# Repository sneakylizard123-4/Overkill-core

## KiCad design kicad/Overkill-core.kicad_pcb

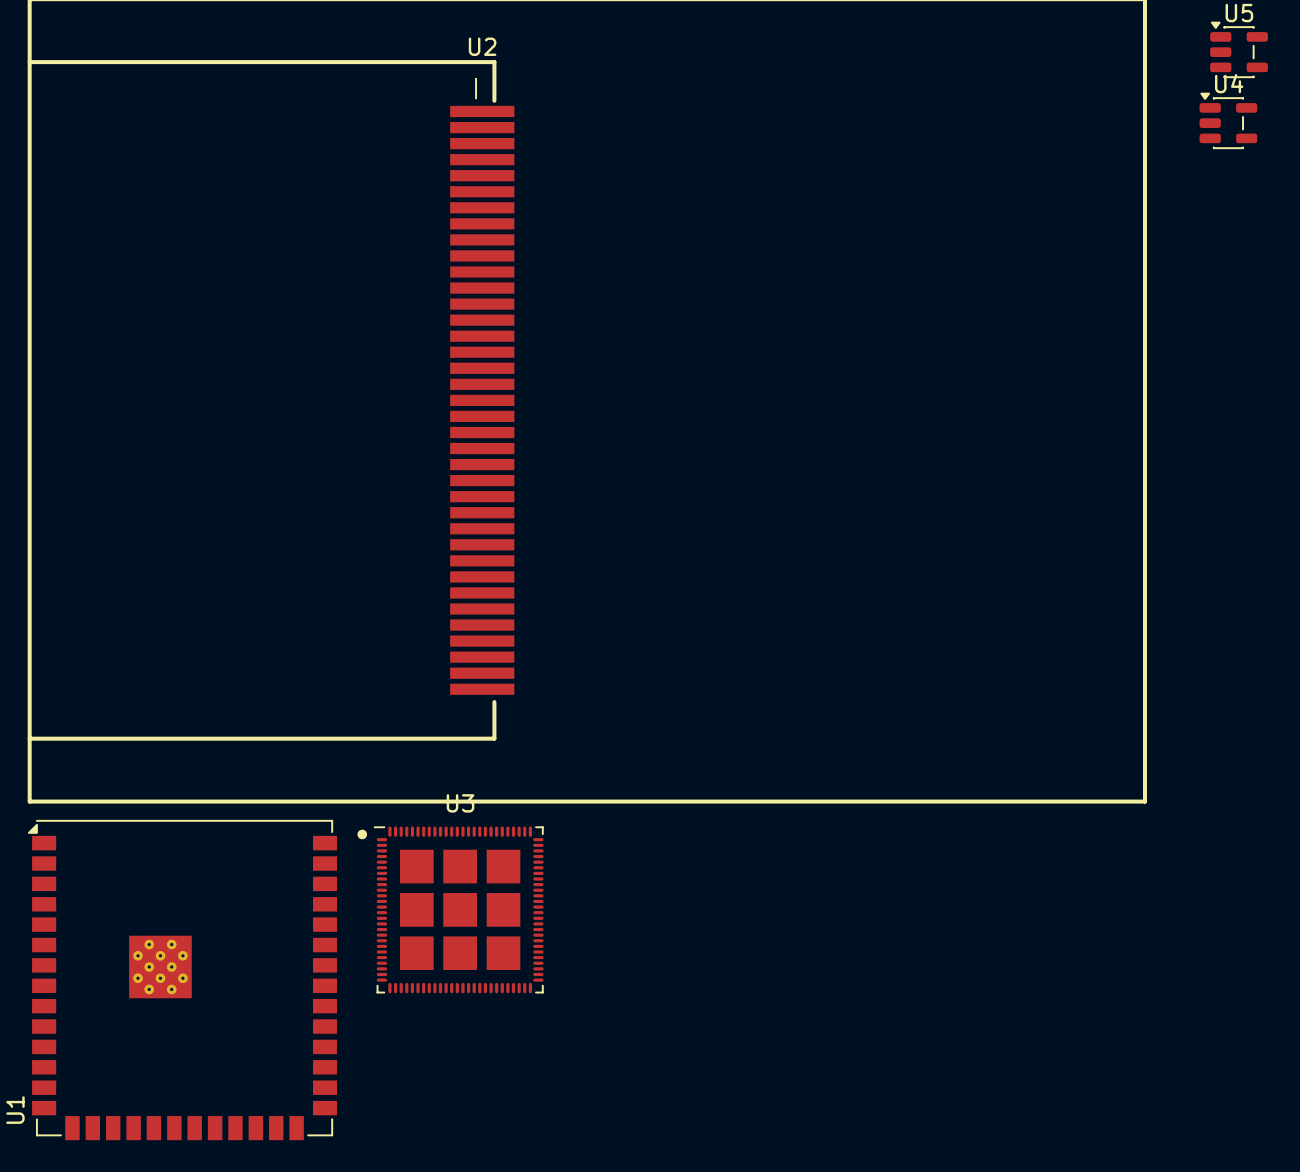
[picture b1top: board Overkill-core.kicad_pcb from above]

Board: 2 copper layers, 5 parts (0 on the bottom side), 3 nets, no tracks yet.

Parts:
U1: ESP32-S3-WROOM-1U
U2: HS28QI084RX; LCD-SMD_HS28QI084RX_1
U3: ESP32-P4
U4: TLV75733PDBV; SOT-23-5
U5: TLV75728PDBV; SOT-23-5

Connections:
+5V: U4.1 (IN), U4.3 (EN), U5.1 (IN)
GND: U4.2 (GND), U5.2 (GND)
unnamed: U1.1 (GND), U1.40 (GND), U1.41 (GND)

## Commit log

2026-05-13 initial
2026-05-13 route chips
2026-05-13 add usb-uart circuitry
2026-05-14 organize
2026-05-14 small updates
2026-05-14 add readme
